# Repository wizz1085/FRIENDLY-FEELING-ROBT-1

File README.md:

# FRIENDLY-FEELING-ROBT
Es un robot compañero el cual te brinda amistad y compañia e interactua con el usuario , por medio de una aplicacion el robot reproduce musica , se maneja por el control de la aplicacion, tambien interactua contigo cuando le hablas cambiando el color de sus ojitos de esta manera mejorando el estado de animo del usuario.
# INTEGRANTES
.Isabella Micolta Del Guercio
                                                                                                                                                                        
.Maryuri catalina medina rojas
                                                                                                                                                                        
.Nicolas palacios quimbayo
# DESCRIPCION
Presentamos friendly feeling robt como una alternativa la cual ayuda con la soledad, depresion ,ansiedad, el prototipo tiene como proposito por medio de su diseño ser util y de facil movilidad, el cual tiene su diseño circular como objetivo de poder acompañarte a todos lados, pensado como solucion al estres y ayudar a las personas antisociales o introvertidas a poder comunicarse mejor o ser personas mas abiertas, para facilitar la socializacion con su entorno.

# OBJETIVOS
.Proveer apoyo emocional mediante un dispositivo que reacciona positivamente a estímulos y comandos

Crear una experiencia positiva y útil para el usuario mejorar el estado de ánimo del usuario.
                                                                                                                                                                      
.Facilitar la integración de la tecnología robótica en la vida cotidiana.

# MISION
Desarrollar un dispositivo interactivo y accesible que, mediante la integración de tecnología robótica y móvil, proporcione apoyo emocional y acompañamiento a personas de todas las edades, mejorando su bienestar emocional a través de respuestas positivas y personalizadas que fomenten la conexión afectiva y la empatía.

# ALCANCE DEL PROYECTO
aproximadamente se tiene estimado que lo puedan adquirir personas entre los 12-65 años, lo cual es un estima del  33.6 y 36 millones de personas en Colombia , porcentualmente estariamos hablando de 75% de la poblacion colombiana, asi que el proyecto abarca ampliamente el mercado nacional.

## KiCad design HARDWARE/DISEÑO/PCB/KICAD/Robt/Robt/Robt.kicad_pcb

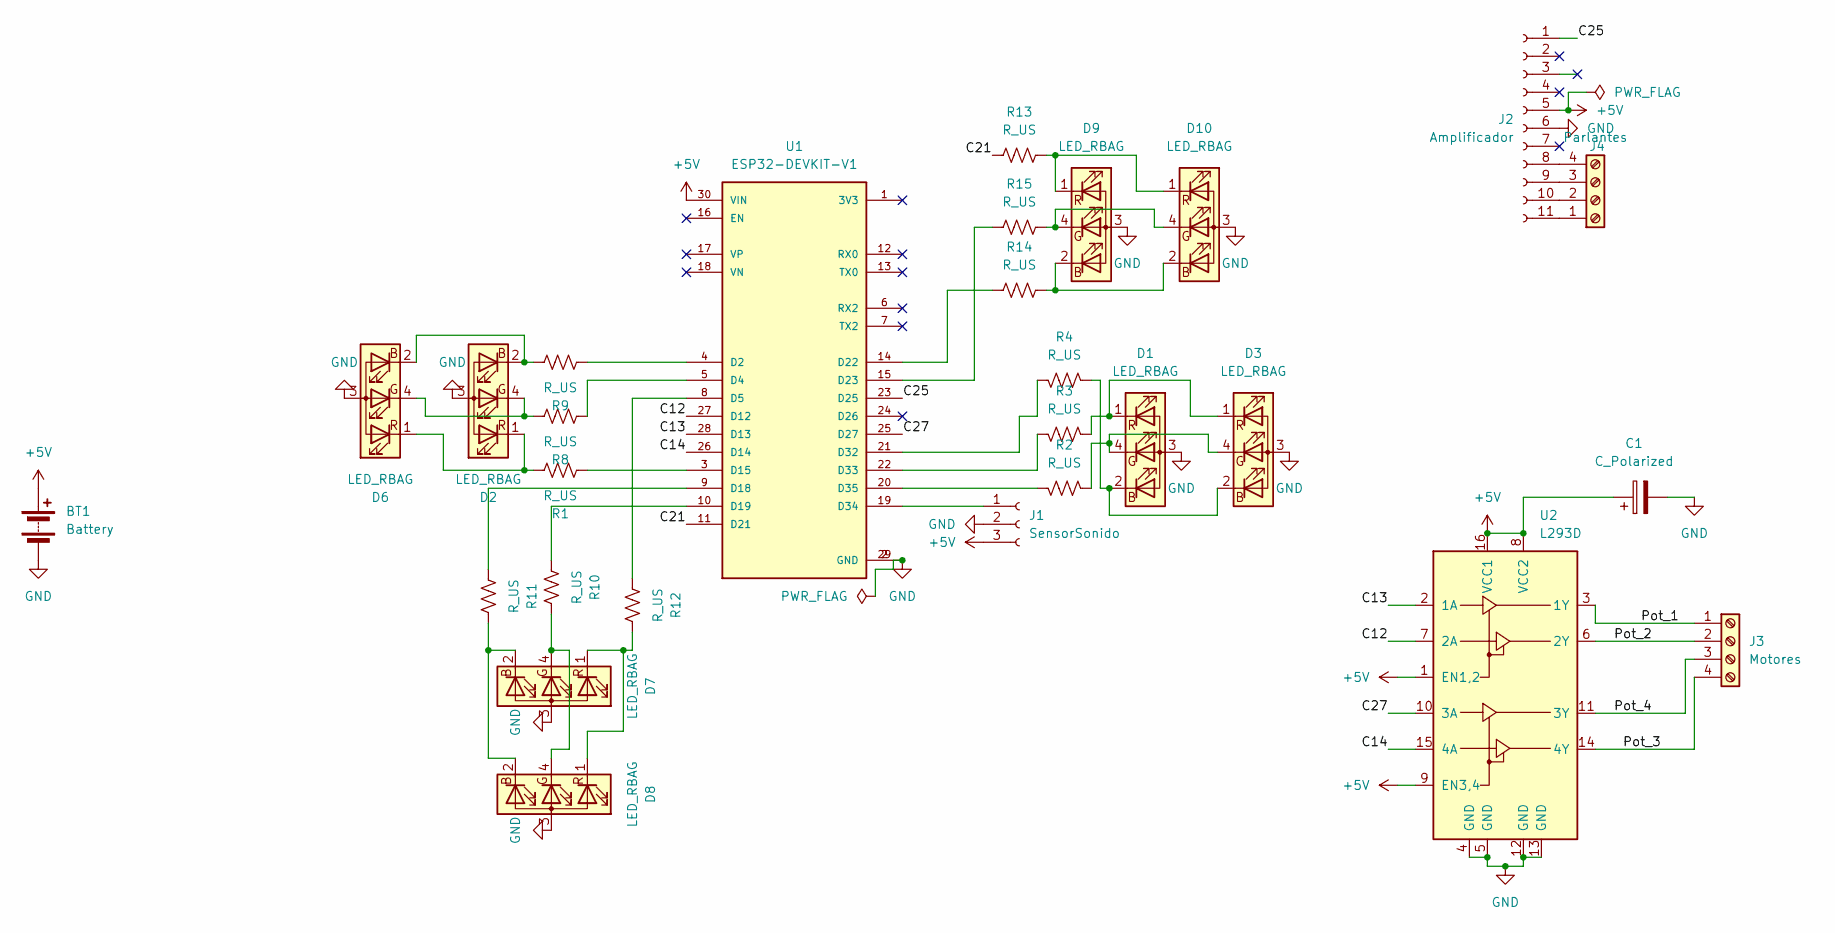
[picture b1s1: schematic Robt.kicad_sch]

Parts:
BT1: Battery; PinSocket_1x02_P2.54mm_Vertical
C1: C_Polarized; CP_Radial_D5.0mm_P2.00mm
D1, D2, D3, D6, D7, D8, D9, D10: LED_RBAG; LED_D5.0mm-4_RGB_Wide_Pins
J1: SensorSonido; PinSocket_1x03_P2.54mm_Vertical
J2: Amplificador; PinSocket_1x11_P2.54mm_Vertical
J3: Motores; TerminalBlock_bornier-4_P5.08mm
J4: Parlantes; TerminalBlock_bornier-4_P5.08mm
R1, R2, R3, R4, R8, R9, R10, R11, R12, R13, R14, R15: R_US; R_Axial_DIN0207_L6.3mm_D2.5mm_P7.62mm_Horizontal
U1: ESP32-DEVKIT-V1; MODULE_ESP32_DEVKIT_V1; PARTREV N/A
U2: L293D; DIP-16_W7.62mm

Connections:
+5V: BT1.1 (+), C1.1, J1.3, J2.5, U1.30 (VIN), U2.1 (EN1,2), U2.8 (VCC2), U2.9 (EN3,4), U2.16 (VCC1)
/C12: U1.27 (D12), U2.7 (2A)
/C13: U1.28 (D13), U2.2 (1A)
/C14: U1.26 (D14), U2.15 (4A)
/C21: R13.2, U1.11 (D21)
/C25: J2.1, U1.23 (D25)
/C27: U1.25 (D27), U2.10 (3A)
/Pot_1: J3.1, U2.3 (1Y)
/Pot_2: J3.2, U2.6 (2Y)
/Pot_3: J3.4, U2.14 (4Y)
/Pot_4: J3.3, U2.11 (3Y)
GND: BT1.2 (-), C1.2, D1.3 (A), D2.3 (A), D3.3 (A), D6.3 (A), D7.3 (A), D8.3 (A), D9.3 (A), D10.3 (A), J1.2, J2.6, U1.2 (GND), U1.29 (GND), U2.4 (GND), U2.5 (GND), U2.12 (GND), U2.13 (GND)
unnamed: D1.2 (BK), D3.2 (BK), R4.2
unnamed: D1.4 (GK), D3.4 (GK), R2.2
unnamed: D1.1 (RK), D3.1 (RK), R3.2
unnamed: D2.2 (BK), D6.2 (BK), R9.1
unnamed: D2.4 (GK), D6.4 (GK), R8.1
unnamed: D2.1 (RK), D6.1 (RK), R1.1
unnamed: D7.2 (BK), D8.2 (BK), R11.1
unnamed: D7.4 (GK), D8.4 (GK), R10.1
unnamed: D7.1 (RK), D8.1 (RK), R12.1
unnamed: D9.2 (BK), D10.2 (BK), R14.1
unnamed: D9.4 (GK), D10.4 (GK), R15.1
unnamed: D9.1 (RK), D10.1 (RK), R13.1
unnamed: J1.1, U1.19 (D34)
unnamed: J2.8, J4.4
unnamed: J2.9, J4.3
unnamed: J2.10, J4.2
unnamed: J2.11, J4.1
unnamed: R9.2, U1.4 (D2)
unnamed: R8.2, U1.5 (D4)
unnamed: R12.2, U1.8 (D5)
unnamed: R1.2, U1.3 (D15)
unnamed: R11.2, U1.9 (D18)
unnamed: R10.2, U1.10 (D19)
unnamed: R14.2, U1.14 (D22)
unnamed: R15.2, U1.15 (D23)
unnamed: R4.1, U1.21 (D32)
unnamed: R3.1, U1.22 (D33)
unnamed: R2.1, U1.20 (D35)

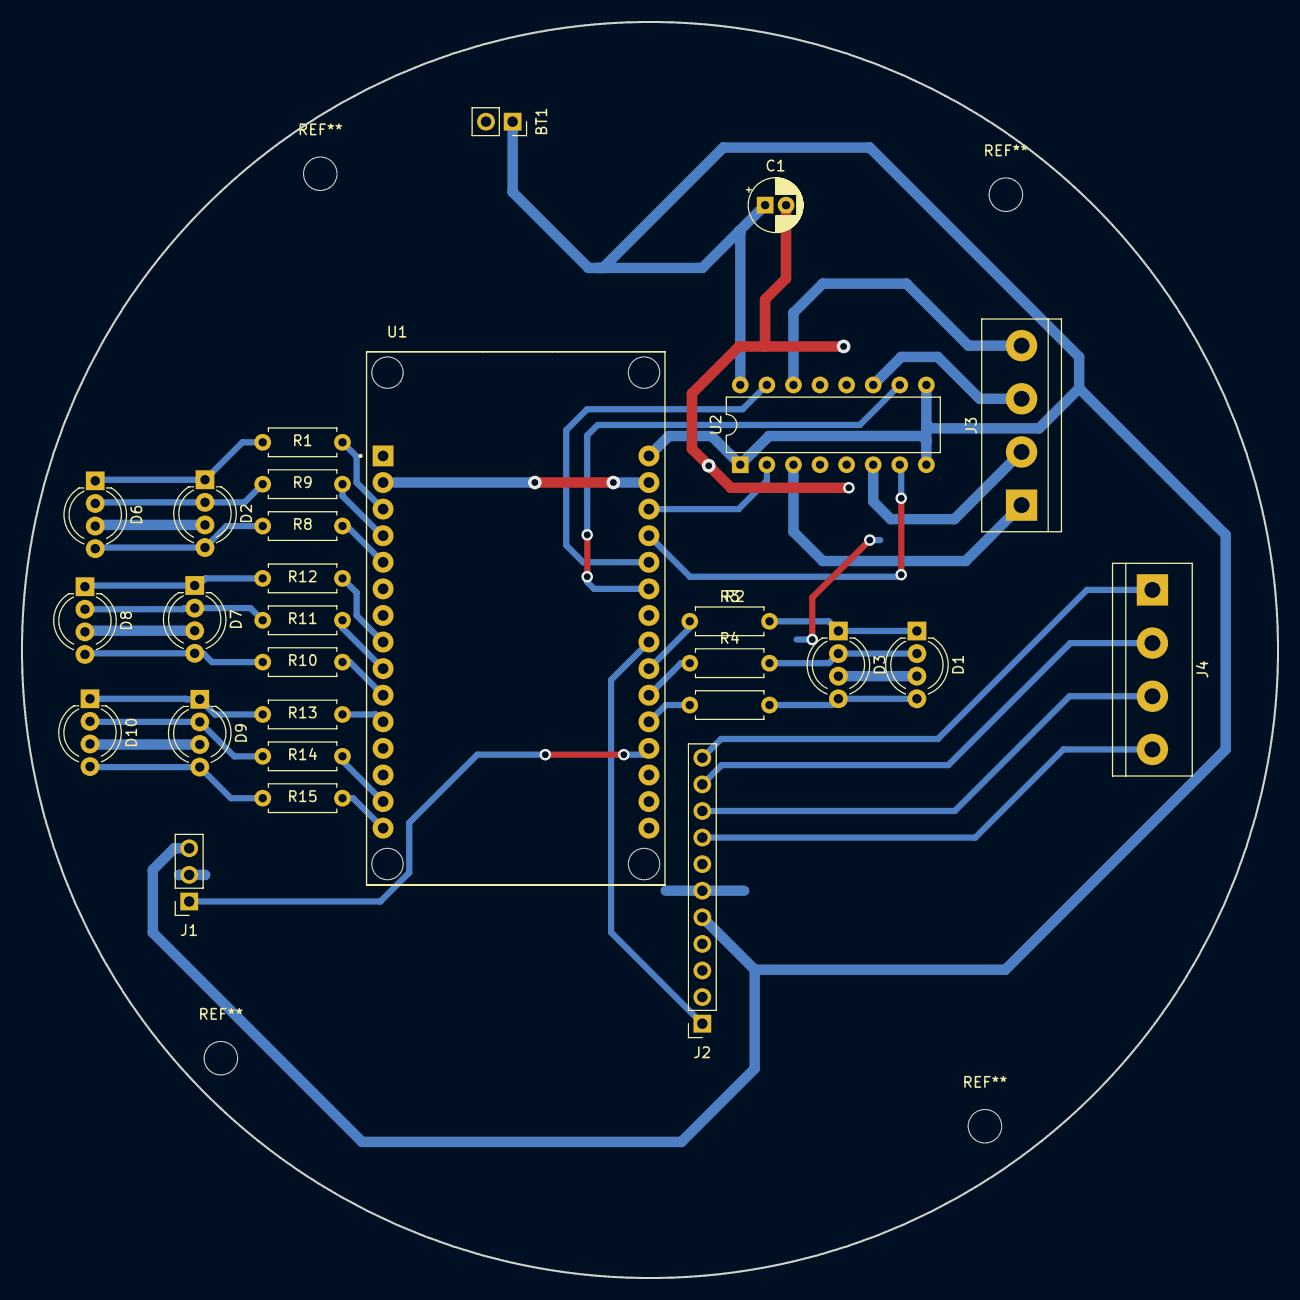
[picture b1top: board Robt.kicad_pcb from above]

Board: 2 copper layers, 120.0 x 120.0 mm, 28 parts (0 on the bottom side), 40 nets.

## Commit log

2024-09-18 CODIGO BLUETOOTH
    código bluetooth
2024-09-18 CÖDIGO GENERAL
    código general
2024-09-18 CÓDIGO DE AUDIO
    código de audio
2024-09-26 poster
2024-09-26 Create MYCROPYTHON
2024-09-26 Create CODIGOS
2024-09-26 CODIGOS
2024-09-26 Create CODIGO GENERAL
2024-09-26 Create CODIGO AUDIO
